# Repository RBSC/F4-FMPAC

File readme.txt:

F4/FMPAC Combo Board version 1.5
Copyright (c) 2016-2025 RBSC
Portions (c) Kamil Karimov

Connection to the mainboard
---------------------------

The board requires a few wires to be connected to the MSX mainboard. The +12v and -12v are required for the FM chip and the
amplifier and must be connected to the JP1 connector. Also the GND (ground) must be connected to JP1, especially if the SJ3
solder jumper stays open. Those voltages and ground can be taken from the side slot of Yamaha MSX2 computers (YIS503, CX5M2
or CX7). On other computers those voltages could be taken from one of the slots or from the power supply's connection to the
mainboard.

The CE pin of the JP2 connector must be connected to the available STLSEL signal. On Yamaha MSX2 computers this could be taken
from the front slot (3.1). On other computers any unused slot signal could be used. The OE pin must be connected to CS1 signal
of the selected slot. However, in case of 27C512 EPROM installation, this pin must be connected to RD signal.

Audio connections
-----------------

The board has 2 different mono audio outputs marked as AMP and SLT. The AMP pin of JP3 must be only connected to the mixer point
of the internal amplifier, where all other SNDIN pins of cartridge slots are connected to. The AMP circuit already contains the
necessary resistor and capacitor and can be directly connected to the amplifier's input. To avoid interference from the other
components it's recommended to use the shielded wire. The shield should be connected to the GND pin of JP3.

The SLT pin of JP3 must be only connected to pin 49 (SNDIN) of any cartridge slot. On Yamaha MSX2 YIS503 and similar computers
the best place to connect the SLT pin is pin 59 on the side slot. Please be careful when connecting the wires - if not sure -
measure the voltages before connecting the wires. In correct connection could result in a damage for the board!

BIOS versions
-------------

The EPROM of the board contains 2 different FMPAC BIOSes. One is for external FMPAC (cartridge), the other is for internal FMPAC
(built-in into MSX2+). The BIOS is selected by JP4 jumper. It is recommended to use the internal FMPAC BIOS with the board. For
this option the jumper should not be installed.

Please pay special attention on the configuration notes on the board for solder jumpers SJ1 and SJ2! Those jumpers must be
configured correctly depending on the used EPROM chip. Otherwise FMPAC's BIOS will not work and there will be no FM music and
sounds in Basic as well as in certain games that detect the BIOS.

Notes
-----

The solderable jumper SJ3 is used to separate digital and analogue grounds. The board works fine without this jumper as long as
you connect the GND wire to JP1. The SJ3 should be only soldered if you don't connect GND to the board. But if you hear any
digital interference in the audio channel after you bridged the SJ3 jumper, please remove the bridge and connect GND wire to JP1.

The F4 Register part of the board is optional. It is only needed when the board is being installed into a computer that is converted
to MSX2+. Normal MSX1 or MSX2 computers don't need F4 port.

This FMPAC board does not support writing anything to SRAM (there's no SRAM on board). Also this device only provides mono sounds
and music. Stereo is not available.

Please note that the provided FMPAC BIOS image doesn't contain the UI (user interface). The full version of the FMPAC BIOS is
available in the RBSC's Carnivore2 cartridge. The BIOS is even translated into English.

IMPORTANT!
----------

The RBSC provides all the files and information for free, without any liability (see the disclaimer.txt file). The provided information,
software or hardware must not be used for commercial purposes unless permitted by the RBSC. Producing a small amount of bare boards for
personal projects and selling the rest of the batch is allowed without the permission of RBSC.

When the sources of the tools are used to create alternative projects, please always mention the original source and the copyright!

Contact information
-------------------

The members of RBSC group Tnt23, Wierzbowsky, Pyhesty, Ptero, GreyWolf, SuperMax, VWarlock, Alspru and DJS3000 can be contacted via the
group's e-mail address:

info@rbsc.su

The group's coordinator could be reached via this e-mail address:

admin@rbsc.su

The group's website can be found here:

https://rbsc.su/
https://rbsc.su/ru

The RBSC's hardware repository can be found here:

https://github.com/rbsc

The RBSC's 3D model repository can be found here:

https://www.thingiverse.com/groups/rbsc/things

-= ! MSX FOREVER ! =-

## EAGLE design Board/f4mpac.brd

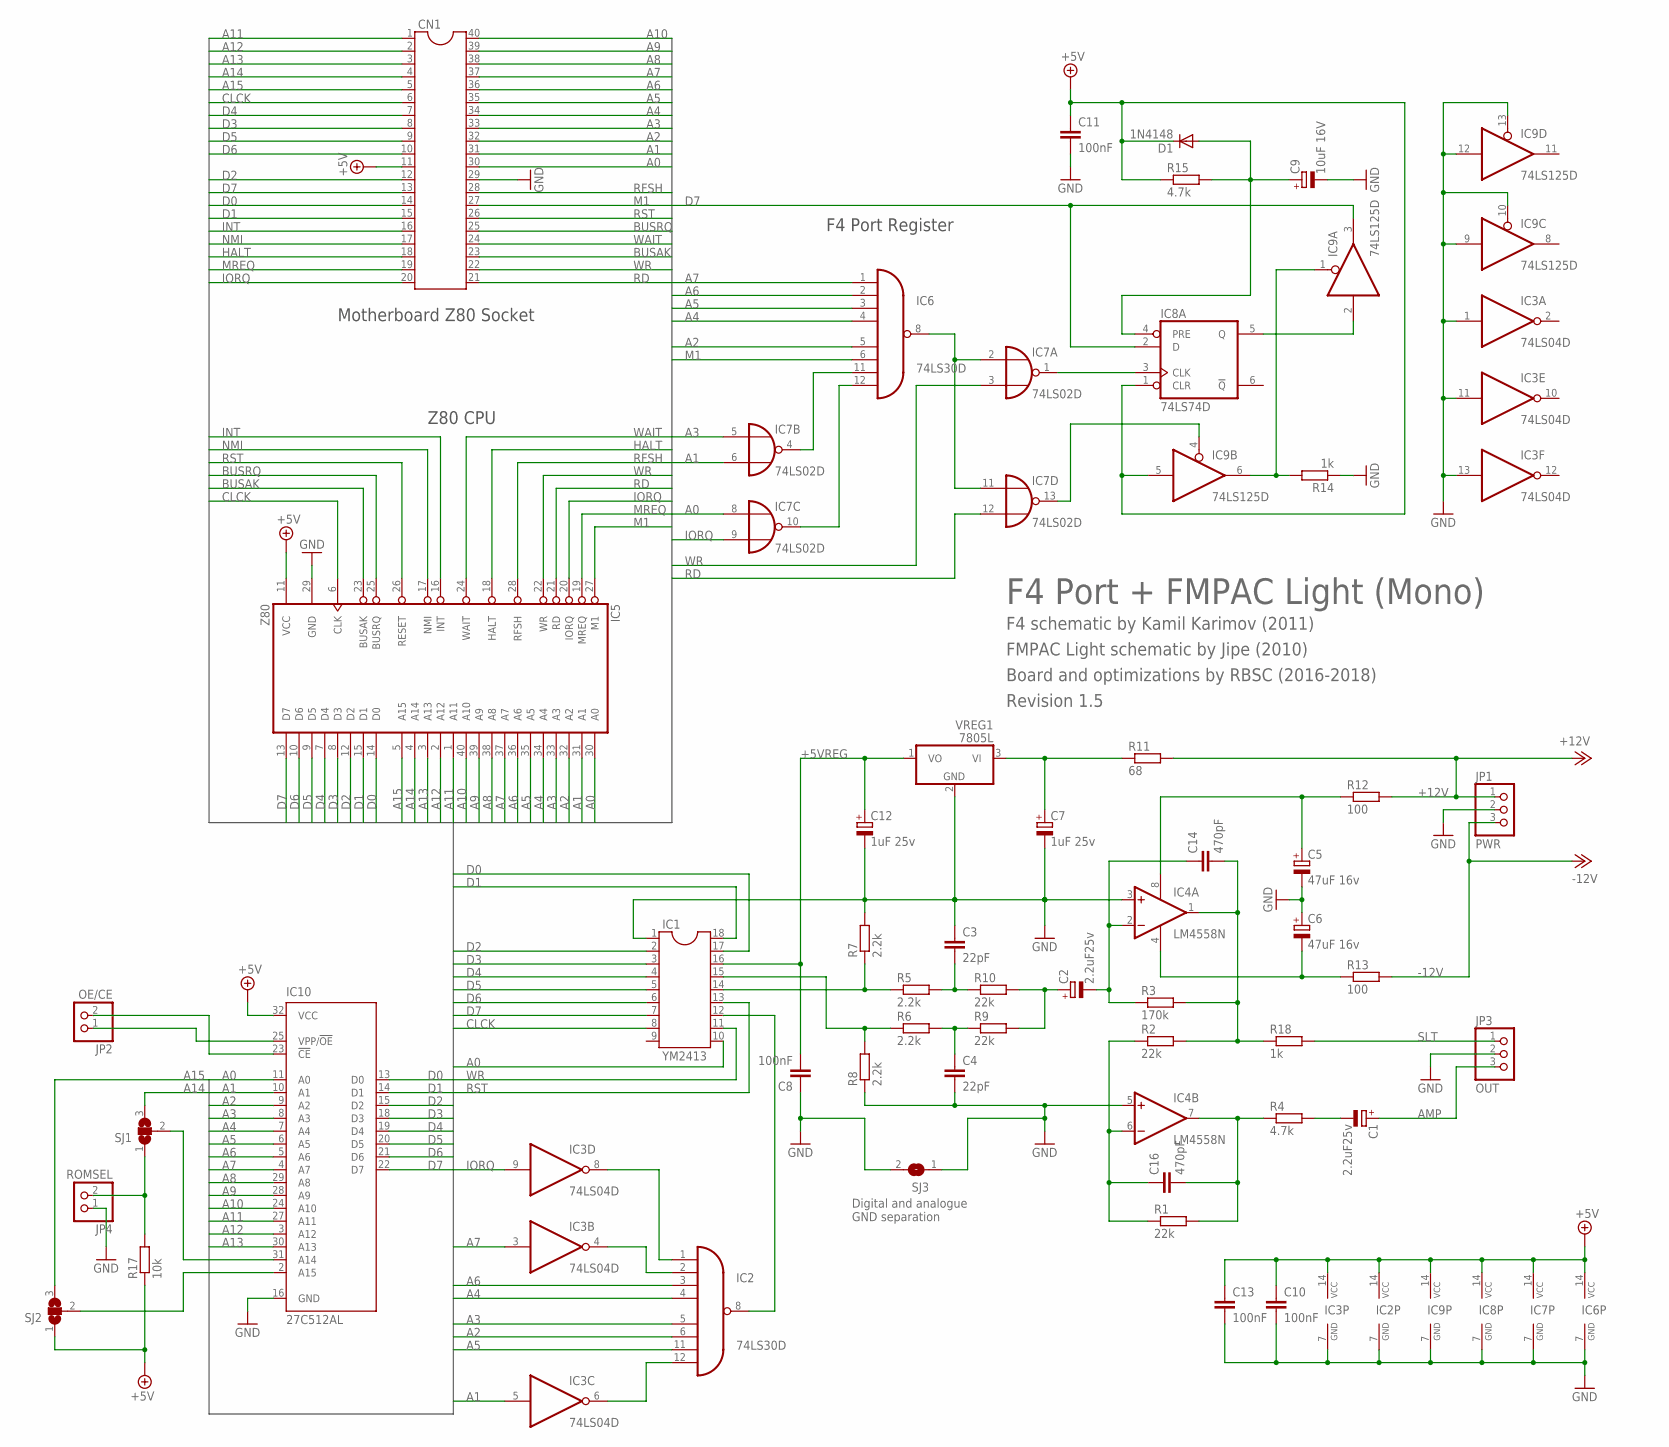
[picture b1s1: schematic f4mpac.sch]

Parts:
C1, C2: 2.2uF25v; SMC_B
C3, C4: 22pF; C0805
C5, C6: 47uF 16v; SMC_C
C7, C12: 1uF 25v; SMC_B
C8, C10, C11, C13: 100nF; C0805
C9: 10uF 16V; SMC_B
C14, C16: 470pF; C0805
CN1: DIP40 MB CONN; DIL40
D1: 1N4148; MINIMELF
IC1: YM2413; DIL18
IC2, IC6: 74LS30D; SO14
IC3: 74LS04D; SO14
IC4: LM4558N; DIL08
IC5: Z80; DIL40
IC7: 74LS02D; SO14
IC8: 74LS74D; SO14
IC9: 74LS125D; SO14
IC10: 27C512AL; PLCC-32
JP1: PWR; 1X03/90
JP2: OE/CE; 1X02/90
JP3: OUT; 1X03/90
JP4: ROMSEL; 1X02/90
R1, R2, R9, R10: 22k; R0805
R3: 170k; R0805
R4: 4.7k; R0805
R5, R6, R7, R8: 2.2k; R0805
R11: 68; R0805
R12, R13: 100; R0805
R14, R18: 1k; R0805
R15: 4.7k; M0805
R17: 10k; R0805
SJ1, SJ2: SJ2W; SJ_2
SJ3: SJ
VREG1: 7805L; TO92

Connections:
+5V: C10.1, C11.1, C13.1, CN1.11, D1.C, IC2.14 (VCC), IC3.14 (VCC), IC5.11 (VCC), IC6.14 (VCC), IC7.14 (VCC), IC8.1 (CLR), IC8.14 (VCC), IC9.5 (I), IC9.14 (VCC), IC10.32 (VCC), R15.1, R17.1, SJ2.1
+5VREG: C8.2, C12.+, IC1.16, VREG1.1 (VO)
+12V: JP1.1, R11.2, R12.2
+12VAMP: C5.+, IC4.8 (V+), R12.1
-12V: JP1.3, R13.2
-12VAMP: C6.-, IC4.4 (V-), R13.1
A0: CN1.30, IC1.10, IC5.30 (A0), IC7.8 (I0), IC10.11 (A0)
A1: CN1.31, IC3.5 (I), IC5.31 (A1), IC7.6 (I1), IC10.10 (A1)
A2: CN1.32, IC2.6 (I5), IC5.32 (A2), IC6.5 (I4), IC10.9 (A2)
A3: CN1.33, IC2.5 (I4), IC5.33 (A3), IC7.5 (I0), IC10.8 (A3)
A4: CN1.34, IC2.4 (I3), IC5.34 (A4), IC6.4 (I3), IC10.7 (A4)
A5: CN1.35, IC2.11 (I6), IC5.35 (A5), IC6.3 (I2), IC10.6 (A5)
A6: CN1.36, IC2.3 (I2), IC5.36 (A6), IC6.2 (I1), IC10.5 (A6)
A7: CN1.37, IC3.3 (I), IC5.37 (A7), IC6.1 (I0), IC10.4 (A7)
A8: CN1.38, IC5.38 (A8), IC10.29 (A8)
A9: CN1.39, IC5.39 (A9), IC10.28 (A9)
A10: CN1.40, IC5.40 (A10), IC10.24 (A10)
A11: CN1.1, IC5.1 (A11), IC10.27 (A11)
A12: CN1.2, IC5.2 (A12), IC10.3 (A12)
A13: CN1.3, IC5.3 (A13), IC10.30 (A13)
A14: CN1.4, IC5.4 (A14), SJ1.3
A15: CN1.5, IC5.5 (A15), SJ2.3
AMP: C1.+, JP3.3
BUSAK: CN1.23, IC5.23 (BUSAK)
BUSRQ: CN1.25, IC5.25 (BUSRQ)
CLCK: CN1.6, IC1.8, IC5.6 (CLK)
D0: CN1.14, IC1.17, IC5.14 (D0), IC10.13 (D0)
D1: CN1.15, IC1.18, IC5.15 (D1), IC10.14 (D1)
D2: CN1.12, IC1.2, IC5.12 (D2), IC10.15 (D2)
D3: CN1.8, IC1.3, IC5.8 (D3), IC10.18 (D3)
D4: CN1.7, IC1.4, IC5.7 (D4), IC10.19 (D4)
D5: CN1.9, IC1.5, IC5.9 (D5), IC10.20 (D5)
D6: CN1.10, IC1.6, IC5.10 (D6), IC10.21 (D6)
D7: CN1.13, IC1.7, IC5.13 (D7), IC8.2 (D), IC9.3 (O), IC10.22 (D7)
GND: C3.1, C4.2, C5.-, C6.+, C7.-, C8.1, C9.-, C10.2, C11.2, C12.-, C13.2, CN1.29, IC1.1, IC2.7 (GND), IC3.1 (I), IC3.7 (GND), IC3.11 (I), IC3.13 (I), IC4.3 (+IN), IC4.5 (+IN), IC5.29 (GND), IC6.7 (GND), IC7.7 (GND), IC8.7 (GND), IC9.7 (GND), IC9.9 (I), IC9.10 (OE), IC9.12 (I), IC9.13 (OE), IC10.16 (GND), JP1.2, JP3.2, JP4.1, R7.2, R8.1, R14.1, SJ3.1, SJ3.2, VREG1.2 (GND)
HALT: CN1.18, IC5.18 (HALT)
INT: CN1.16, IC5.16 (INT)
IORQ: CN1.20, IC3.9 (I), IC5.20 (IORQ), IC7.9 (I1)
M1: CN1.27, IC5.27 (M1), IC6.6 (I5)
MREQ: CN1.19, IC5.19 (MREQ)
unnamed: IC1.12, IC2.8 (O)
unnamed: IC10.31 (A14), SJ1.2
unnamed: C7.+, R11.1, VREG1.3 (VI)
unnamed: IC1.14, R5.1, R7.1
unnamed: C2.-, C14.1, IC4.2 (-IN), R3.1
unnamed: C16.1, IC4.6 (-IN), R1.1, R2.1
unnamed: C1.-, R4.2
unnamed: C3.2, R5.2, R10.1
unnamed: IC1.15, R6.1, R8.2
unnamed: C4.1, R6.2, R9.1
unnamed: IC2.12 (I7), IC3.6 (O)
unnamed: C2.+, R9.2, R10.2
unnamed: IC2.2 (I1), IC3.4 (O)
unnamed: IC2.1 (I0), IC3.8 (O)
unnamed: C9.+, D1.A, IC8.4 (PRE), R15.2
unnamed: IC10.25 (VPP/!OE), JP2.1
unnamed: IC10.23 (!CE), JP2.2
unnamed: JP4.2, R17.2, SJ1.1
unnamed: IC6.11 (I6), IC7.4 (O)
unnamed: IC10.2 (A15), SJ2.2
unnamed: C16.2, IC4.7 (OUT), R1.2, R4.1
unnamed: IC6.12 (I7), IC7.10 (O)
unnamed: IC7.1 (O), IC8.3 (CLK)
unnamed: IC7.13 (O), IC9.4 (OE)
unnamed: IC6.8 (O), IC7.2 (I0), IC7.11 (I0)
unnamed: IC9.1 (OE), IC9.6 (O), R14.2
unnamed: C14.2, IC4.1 (OUT), R2.2, R3.2, R18.1
unnamed: IC8.5 (Q), IC9.2 (I)
NMI: CN1.17, IC5.17 (NMI)
RD: CN1.21, IC5.21 (RD), IC7.12 (I1)
RFSH: CN1.28, IC5.28 (RFSH)
RST: CN1.26, IC1.13, IC5.26 (RESET)
SLT: JP3.1, R18.2
WAIT: CN1.24, IC5.24 (WAIT)
WR: CN1.22, IC1.11, IC5.22 (WR), IC7.3 (I1)

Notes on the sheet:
F4 Port Register
Z80 CPU
Motherboard Z80 Socket
F4 schematic by Kamil Karimov (2011)
FMPAC Light schematic by Jipe (2010)
F4 Port + FMPAC Light (Mono)
Board and optimizations by RBSC (2016-2018)
Digital and analogue GND separation
Revision 1.5

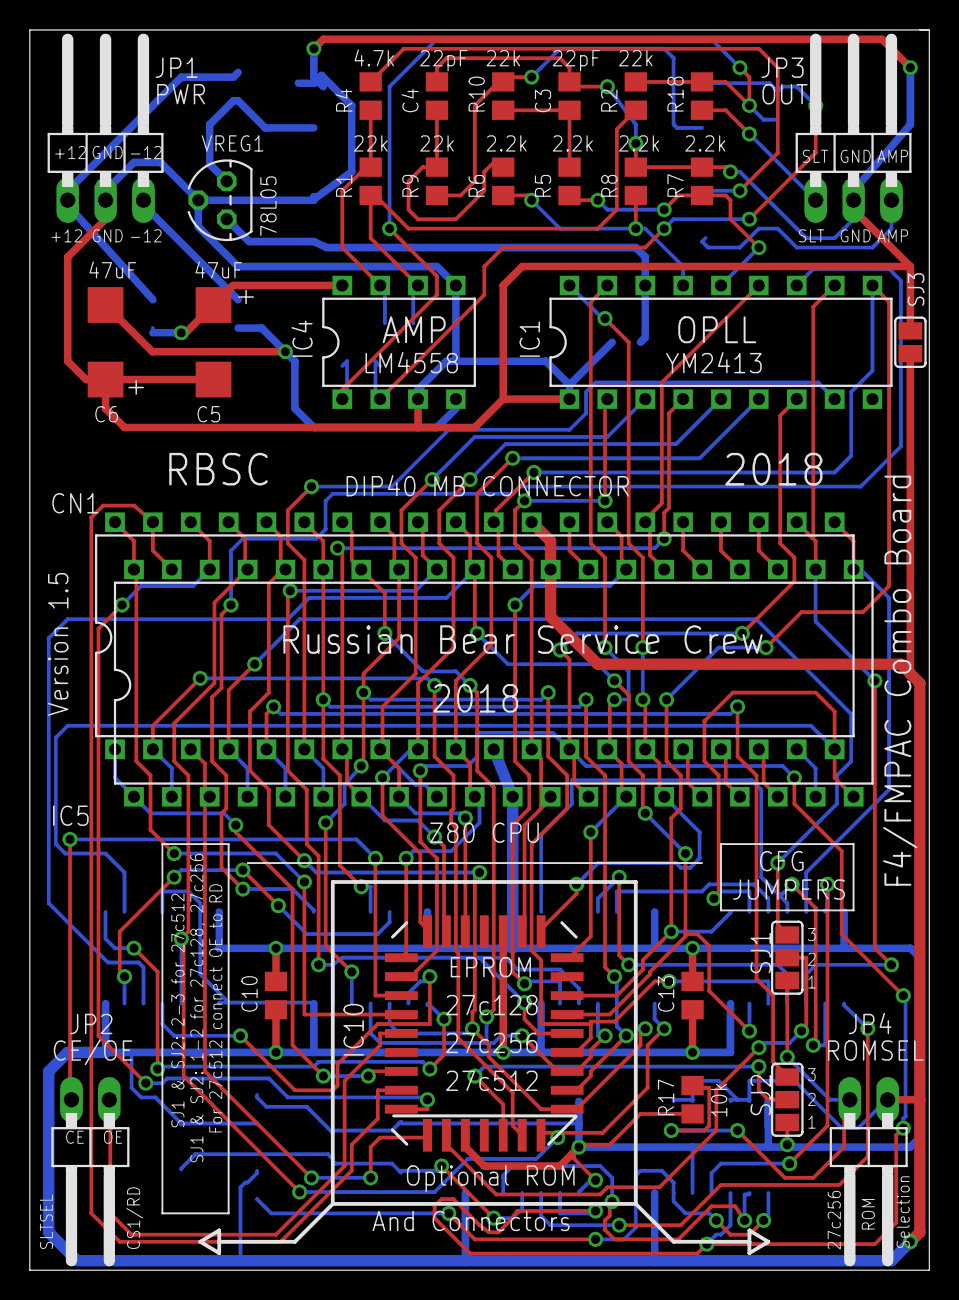
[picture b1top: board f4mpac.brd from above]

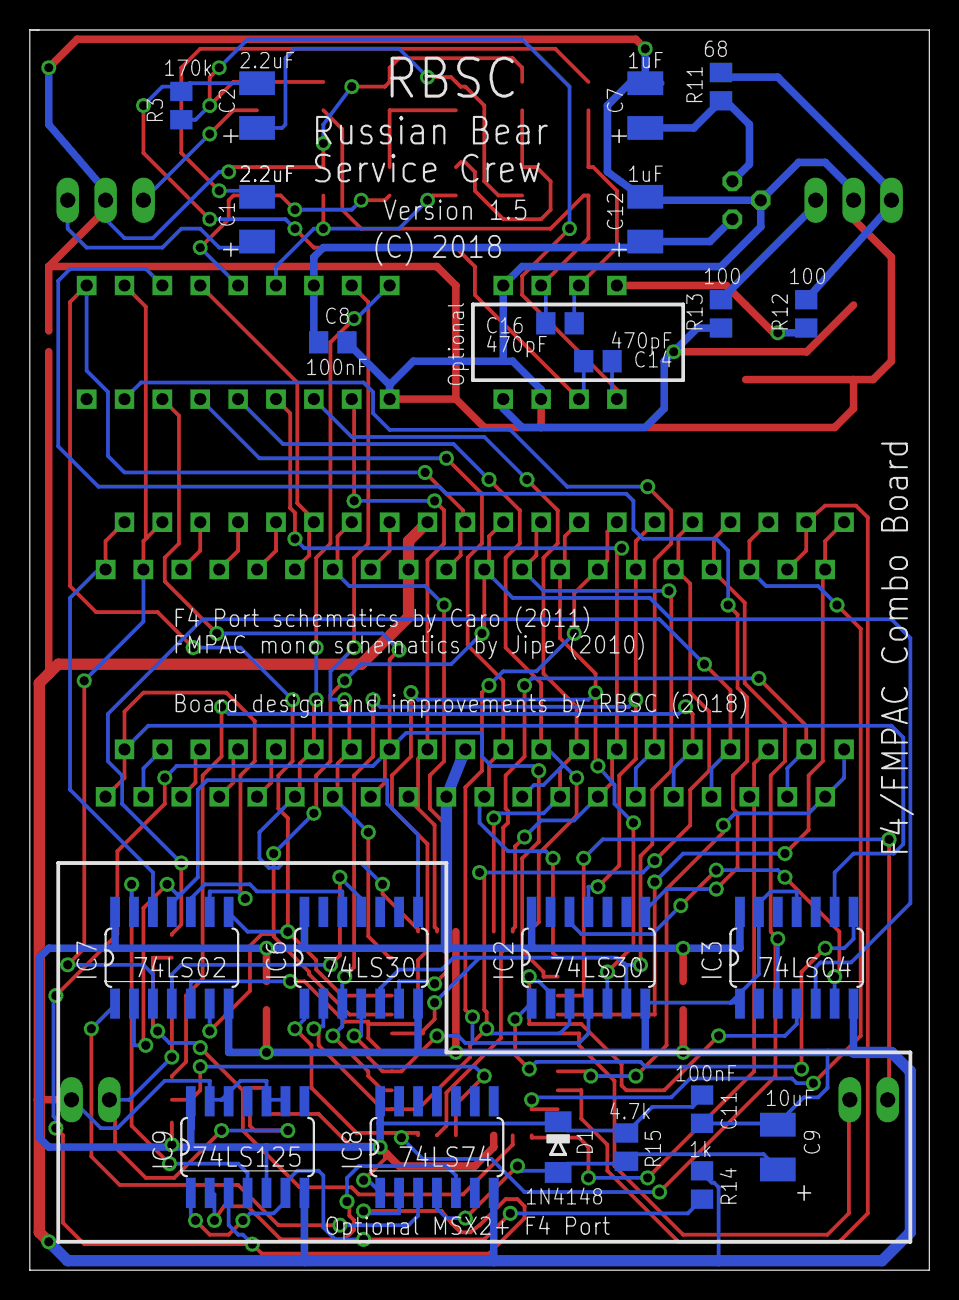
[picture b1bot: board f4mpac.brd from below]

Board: 2 copper layers, 60.3 x 83.2 mm, 52 parts (22 on the bottom side), 75 nets.

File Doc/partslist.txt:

Partlist

Part     Value          Device         Package  Library    Sheet

C1       2.2uF25v       CPOL-EUSMCB    SMC_B    rcl        1
C2       2.2uF25v       CPOL-EUSMCB    SMC_B    rcl        1
C3       22pF           C-EUC0805      C0805    rcl        1
C4       22pF           C-EUC0805      C0805    rcl        1
C5       47uF 16v       CPOL-EUSMCC    SMC_C    rcl        1
C6       47uF 16v       CPOL-EUSMCC    SMC_C    rcl        1
C7       1uF 25v        CPOL-EUSMCB    SMC_B    rcl        1
C8       100nF          C-EUC0805      C0805    rcl        1
C9       10uF 16V       CPOL-EUSMCB    SMC_B    rcl        1
C10      100nF          C-EUC0805      C0805    rcl        1
C11      100nF          C-EUC0805      C0805    rcl        1
C12      1uF 25v        CPOL-EUSMCB    SMC_B    rcl        1
C13      100nF          C-EUC0805      C0805    rcl        1
C14      470pF          C-EUC0805      C0805    rcl        1
C16      470pF          C-EUC0805      C0805    rcl        1
CN1      DIP40 MB CONN  DIL40          DIL40    ic-package 1
D1       1N4148         DIODE-MINIMELF MINIMELF diode      1
IC1      YM2413         DIL18          DIL18    ic-package 1
IC2      74LS30D        74LS30D        SO14     74xx-eu    1
IC3      74LS04D        74LS04D        SO14     74xx-eu    1
IC4      LM4558N        LM4558N        DIL08    linear     1
IC5      Z80            Z80CPU         DIL40    zilog      1
IC6      74LS30D        74LS30D        SO14     74xx-eu    1
IC7      74LS02D        74LS02D        SO14     74xx-eu    1
IC8      74LS74D        74LS74D        SO14     74xx-eu    1
IC9      74LS125D       74LS125D       SO14     74xx-eu    1
IC10     27C512AL       27C512AL       PLCC-32  microchip  1
JP1      PWR            PINHD-1X3/90   1X03/90  pinhead    1
JP2      OE/CE          PINHD-1X2/90   1X02/90  pinhead    1
JP3      OUT            PINHD-1X3/90   1X03/90  pinhead    1
JP4      ROMSEL         PINHD-1X2/90   1X02/90  pinhead    1
R1       22k            R-EU_R0805     R0805    rcl        1
R2       22k            R-EU_R0805     R0805    rcl        1
R3       170k           R-EU_R0805     R0805    rcl        1
R4       4.7k           R-EU_R0805     R0805    rcl        1
R5       2.2k           R-EU_R0805     R0805    rcl        1
R6       2.2k           R-EU_R0805     R0805    rcl        1
R7       2.2k           R-EU_R0805     R0805    rcl        1
R8       2.2k           R-EU_R0805     R0805    rcl        1
R9       22k            R-EU_R0805     R0805    rcl        1
R10      22k            R-EU_R0805     R0805    rcl        1
R11      68             R-EU_R0805     R0805    rcl        1
R12      100            R-EU_R0805     R0805    rcl        1
R13      100            R-EU_R0805     R0805    rcl        1
R14      1k             R-EU_R0805     R0805    rcl        1
R15      4.7k           R-EU_M0805     M0805    rcl        1
R17      10k            R-EU_R0805     R0805    rcl        1
R18      1k             R-EU_R0805     R0805    rcl        1
SJ1                     SJ2W           SJ_2     jumper     1
SJ2                     SJ2W           SJ_2     jumper     1
SJ3                     SJ             SJ       jumper     1
VREG1    7805L          7805L          TO92     linear     1

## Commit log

2016-01-26 :tada: Added .gitattributes & .gitignore files
2016-01-26 Version 2 of the board
2016-01-26 Added ROM
2016-03-05 New board version 1.3
    New board version 1.3, new combined and selectable ROM, easier to get
    ROM chip, corrected names error, blocking capacitors, additional noise
    suppressing capacitor
2016-05-27 Partslist and pics
2017-04-26 Updated source and gerber files, added schematics
2017-05-20 Added readme files
2019-01-23 Release 23.01.2019
    Improved board, redrawn schematics
2023-05-14 Updated 14.05.2023
    Small correction on the board for non-critical problem
2025-05-14 Updated 14.05.2025
    Updated the board to version 1.5. Corrected R4, C14 and C16 values. Updated readme file.

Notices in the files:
Board/f4mpac.brd:
(C) 2018
